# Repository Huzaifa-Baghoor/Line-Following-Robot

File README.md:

# Autonomous Line Following Robot

Hi! I wanted to make a Line Following Robot(LFR) and I visited some shops and online marketplaces but I couldn't find a good, fast, compact and accurate robot with a reasonable price. 
So, I created a LFR from scratch including the PCBs for main board and sensor array for the hardware part and code in 5 separate files.
Now I will explain Components, Wiring, Coding, and sensor array separately. 

# Components

I've decided the components based on affordability, speed, availability and ease of use.
Starting with the micro controller I've selected **Raspberry Pi Pico RP2040** because it has much more processing power than Arduino nano and I've not selected ESP 32 because I wanted to make the robot completely offline and autonomous and for motors I've selected **600rpm 6v N20 motors with encoders** for fast speed and high torque to drive these motors I've chosen **TB6612FNG** motor driver because it has low voltage drop and also it is way lighter than L298N. I've used decided to use a 2S Li-Po battery which is about 7.4v which can power the motors with ease and to power Pico I'd use a step down buck converter to convert these 7.4v into 5v so we don't damage the Pico to charge the battery I'd use a 2S charger and for the sensors I've designed a custom sensor array.

##  PCB and Connections

To talk about the connections, I'd Start with the Power connections. The battery provides 7.4v which goes to VMOT pin of motor driver and buck converter. the buck converter then outputs 5v which goes to VSYS on Pico. Now we have 3 voltages. i.e. 7.4v, 5v and 3.3v. now the 3.3v goes to VCC and STBY pin of TB6612FNG and VCC pin on Sensor Array. 
Now lets talk about the Data and Logic Signals. The GPIO pins from 0 to 18 will be connected to sensor array and GPIO pins 19,20, 21, 22, 26, 27 will be connected to PWMA, AIN1, AIN2, PWMB, BIN1 and BIN2 respectively.
At the end the AO1,  AO2 and BO1, BO2 will be connected to left and right motors respectively.
|Schematics|Tracks|
| :---: | :---: |
|  |  |

## Custom Built Sensor Array

Now for the most difficult problem that I've faced in this project. I wanted to get analog sensor readings but Raspberry Pi Pico had only 3 analog pins. So I could add a Multiplexer chip which would make the PCB bulky. So I designed a workaround using an RC discharge Circuit.
Instead of reading analog voltages, I paired 16 TCRT5000 sensors with 10nF capacitors and 220-Ohm Resistors. This converts the analog voltage signal to a digital timing signal.
**Working:** The pico sends a brief signal to charge all 16 capacitors. Then it acts as a high-speed stopwatch to measure how fast each capacitors discharges.
 - If the sensor detects **white surface**, the capacitor discharges **very fast**
 - If the sensor detects **black surface**, the capacitor discharges **slowly**
By doing this, I was able to read 16 analog sensors on 16 digital pins.
To make the array even better, I also integrated two SPDT micro limit switch to use as bump sensors on left and right corners of the PCB. 

|Schematics|Tracks|
| :---: | :---: |
|  |  |

# Bill of Materials (BOM)
After doing my research, the most affordable components I've got are as follows,

| Component | Quantity | Est. Cost (USD) | 
| :--- | :---: | :--- | 
| **Custom PCBs (JLCPCB)** | 2 Sets | $15.00 | 
| **Raspberry Pi Pico** | 1 | $5.00 | 
| **TCRT5000 Transceivers** | 16 | $4.00 | 
| **SMD Passives (0805)** | 32 | $2.00 | 
| **SPDT Limit Switches** | 2 | $1.00 | 
| **TB6612FNG Module** | 1 | $3.00 | 
| **6V N20 Motors (600 RPM)** | 4 | $50.00 | 
| **N20 Wheels & Brackets** | 4 | $6.00 | 
| **2S LiPo Battery (7.4V)** | 1 | $10.00 | 
| **Power Modules** | 2 | $3.00 | 
| **Misc. Hardware** | 1 | $5.00 | 
| **Total Build Cost:** |  | **~$104.00 USD** |

Because I designed the electronics to use standard, readily available modules, The robot is highly modular. If a motor driver or battery charger ever burns out during a competition, I can just unplug it and swap in a $3 replacement without having to desolder or rebuild the entire robot.

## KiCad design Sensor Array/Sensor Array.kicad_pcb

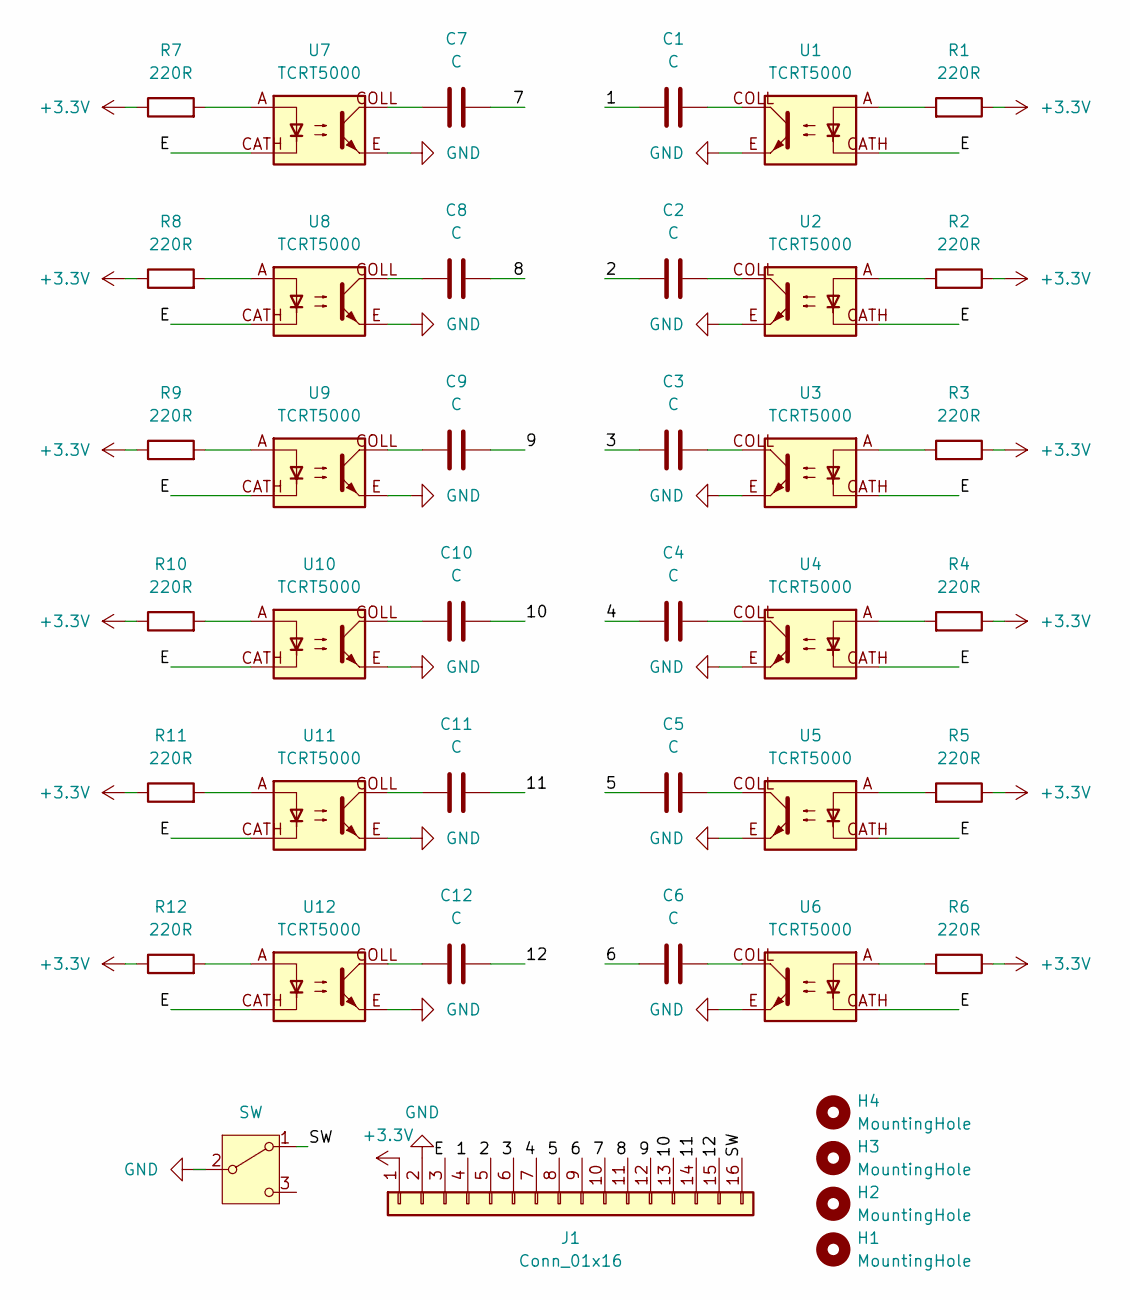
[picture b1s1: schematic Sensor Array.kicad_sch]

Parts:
C1, C2, C3, C4, C5, C6, C7, C8, C9, C10, C11, C12: C; C_0805_2012Metric_Pad1.18x1.45mm_HandSolder
H1, H2, H3, H4: MountingHole; MountingHole_3.2mm_M3
J1: Conn_01x16; PinHeader_1x16_P2.54mm_Horizontal
R1, R2, R3, R4, R5, R6, R7, R8, R9, R10, R11, R12: 220R; R_0805_2012Metric_Pad1.20x1.40mm_HandSolder
SW2: SW; SW_XKB_DM1-16UC-1
U1, U2, U3, U4, U5, U6, U7, U8, U9, U10, U11, U12: TCRT5000; tcrt5000

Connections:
+3.3V: J1.1, R1.1, R2.1, R3.1, R4.1, R5.1, R6.1, R7.1, R8.1, R9.1, R10.1, R11.1, R12.1
/1: C1.2, J1.4
/2: C2.2, J1.5
/3: C3.2, J1.6
/4: C4.2, J1.7
/5: C5.2, J1.8
/6: C6.2, J1.9
/7: C7.2, J1.10
/8: C8.2, J1.11
/9: C9.2, J1.12
/10: C10.2, J1.13
/11: C11.2, J1.14
/12: C12.2, J1.15
/E: J1.3, U1.CATH, U2.CATH, U3.CATH, U4.CATH, U5.CATH, U6.CATH, U7.CATH, U8.CATH, U9.CATH, U10.CATH, U11.CATH, U12.CATH
/SW: J1.16, SW2.1 (A); also elsewhere on the board
GND: J1.2, SW2.2 (B), U1.E, U2.E, U3.E, U4.E, U5.E, U6.E, U7.E, U8.E, U9.E, U10.E, U11.E, U12.E; also elsewhere on the board
unnamed: C1.1, U1.COLL
unnamed: C2.1, U2.COLL
unnamed: C3.1, U3.COLL
unnamed: C4.1, U4.COLL
unnamed: C5.1, U5.COLL
unnamed: C6.1, U6.COLL
unnamed: C7.1, U7.COLL
unnamed: C8.1, U8.COLL
unnamed: C9.1, U9.COLL
unnamed: C10.1, U10.COLL
unnamed: C11.1, U11.COLL
unnamed: C12.1, U12.COLL
unnamed: R1.2, U1.A
unnamed: R2.2, U2.A
unnamed: R3.2, U3.A
unnamed: R4.2, U4.A
unnamed: R5.2, U5.A
unnamed: R6.2, U6.A
unnamed: R7.2, U7.A
unnamed: R8.2, U8.A
unnamed: R9.2, U9.A
unnamed: R10.2, U10.A
unnamed: R11.2, U11.A
unnamed: R12.2, U12.A

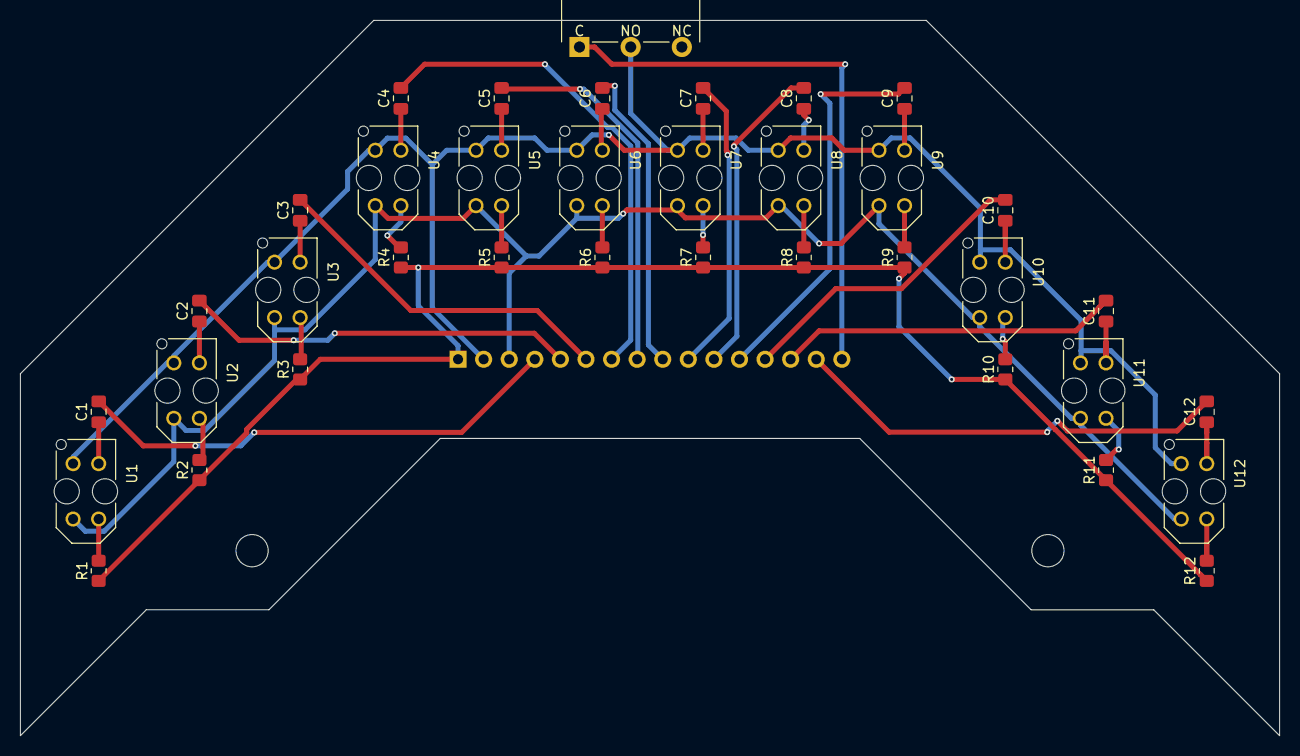
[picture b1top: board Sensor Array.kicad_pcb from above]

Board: 2 copper layers, 125.0 x 71.0 mm, 40 parts (1 on the bottom side), 40 nets.

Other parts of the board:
SW: SW; SW_XKB_DM1-16UC-1

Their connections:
/SW: SW.1 (A); also elsewhere on the board
GND: SW.2 (B); also elsewhere on the board

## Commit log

2026-03-04 Filed
